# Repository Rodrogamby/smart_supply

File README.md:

# Dashboard

Dashboard for the project, built with HTML, CSS, JavaScript, Vite, and MQTT.js

The current prototype displays real sensor readings from an ESP32-S3 in the Channel 1 area

## Requirements

- Install [Node.js](https://nodejs.org/) with npm 
- An internet connection to reach the MQTT broker already running on Azure
- An ESP32 publishing measurements to see live readings

## Install and run

Open a terminal in the GUI folder containing `package.json`.

```sh
npm install
npm run dev
```

`npm install` installs the project's dependencies, including Vite and MQTT.js, and creates `node_modules`. 

Open the local URL printed by Vite. Keep the terminal running while using the dashboard. Press **Ctrl+C** to stop it; use `npm run dev` to start it again.

## Connect to MQTT

Enter these values in the dashboard and click **Connect**:

| Setting | Value |
| --- | --- |
| WebSocket URL | `wss://retotest.mexicocentral.cloudapp.azure.com:8084/mqtt` |
| Current test username | `reto` |
| Current test password | `reto` |
| Topic used by the JavaScript | `test2` |

These are temporary lol

The ESP32 sends MQTT over TLS on port **8883**. The browser uses MQTT over secure WebSockets on port **8084** to connect to the same broker.

## Measurement format

The ESP32 publishes JSON messages like this on `test2`:

```json
{
  "device": "device",
  "sensor": "sensor",
  "sample": 1,
  "adc_raw": 25798
}
```

## Project files

| File | Purpose |
| --- | --- |
| `index.html` | Dashboard structure |
| `src/style.css` | Styling and responsive layout |
| `src/main.js` | MQTT connection, message validation, and display updates |
| `package.json` | Dependencies and npm commands |
| `package-lock.json` | Locked dependency versions |

# Access the Virtual Machine

Use Tec Visitantes Network

```cmd
ssh -i "path of the  smart_supply\VM\vm1_key.pem file" azureuser@158.23.60.51
```

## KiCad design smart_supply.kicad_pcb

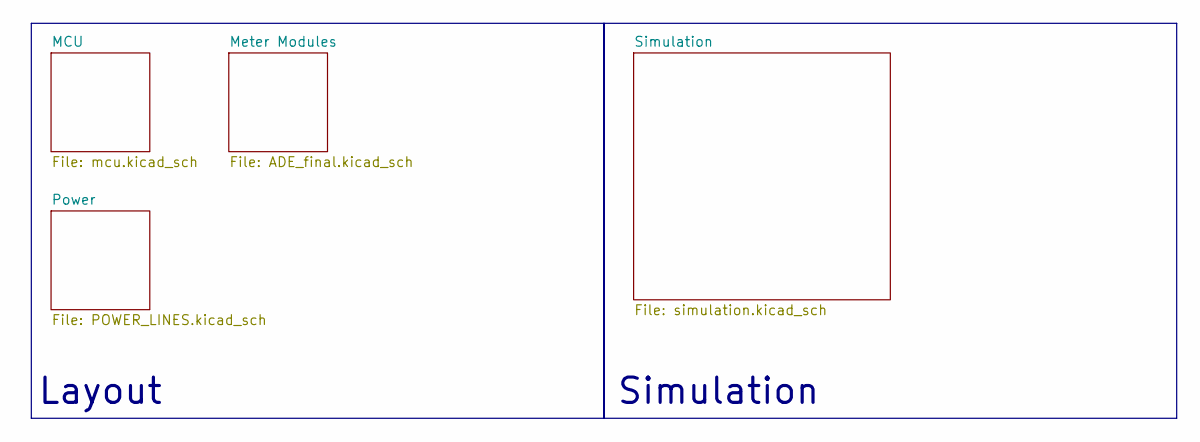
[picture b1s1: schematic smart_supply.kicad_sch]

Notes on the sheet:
Simulation
Layout

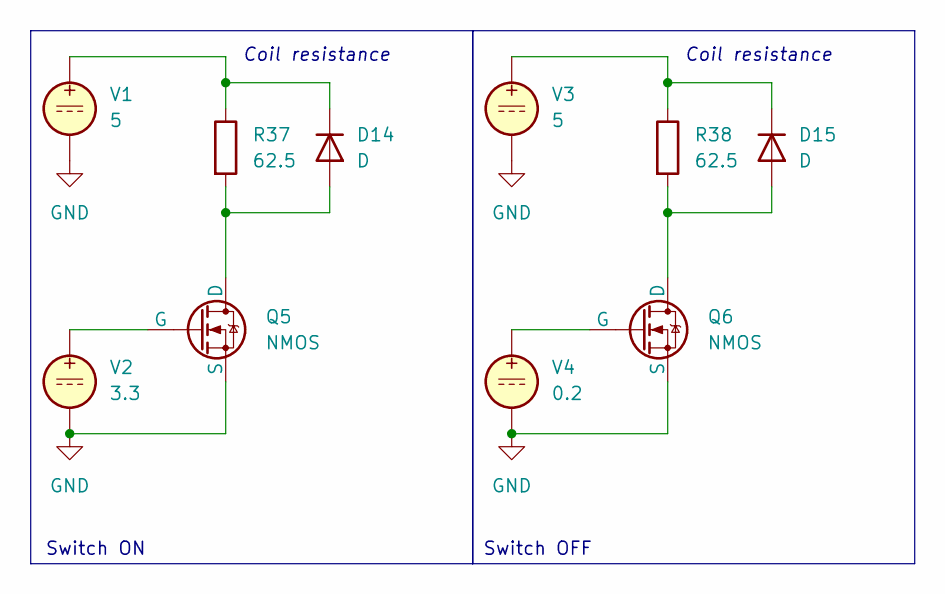
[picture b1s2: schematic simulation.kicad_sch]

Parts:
D14, D15: D
Q5, Q6: NMOS; Relay_SPST_Omron_G2RL-1A-E
R37, R38: 62.5
V1, V3: 5; TQFP-44_10x10mm_P0.8mm
V2: 3.3; TQFP-44_10x10mm_P0.8mm
V4: 0.2; TQFP-44_10x10mm_P0.8mm

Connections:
unnamed: D14.1 (K), R37.1, V1.1
unnamed: D14.2 (A), Q5.1 (D), R37.2
unnamed: D15.1 (K), R38.1, V3.1
unnamed: D15.2 (A), Q6.1 (D), R38.2
unnamed: Q5.2 (G), V2.1
unnamed: Q5.3 (S), Q6.3 (S), V1.2, V2.2, V3.2, V4.2
unnamed: Q6.2 (G), V4.1

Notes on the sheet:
Coil resistance
Switch OFF
Switch ON

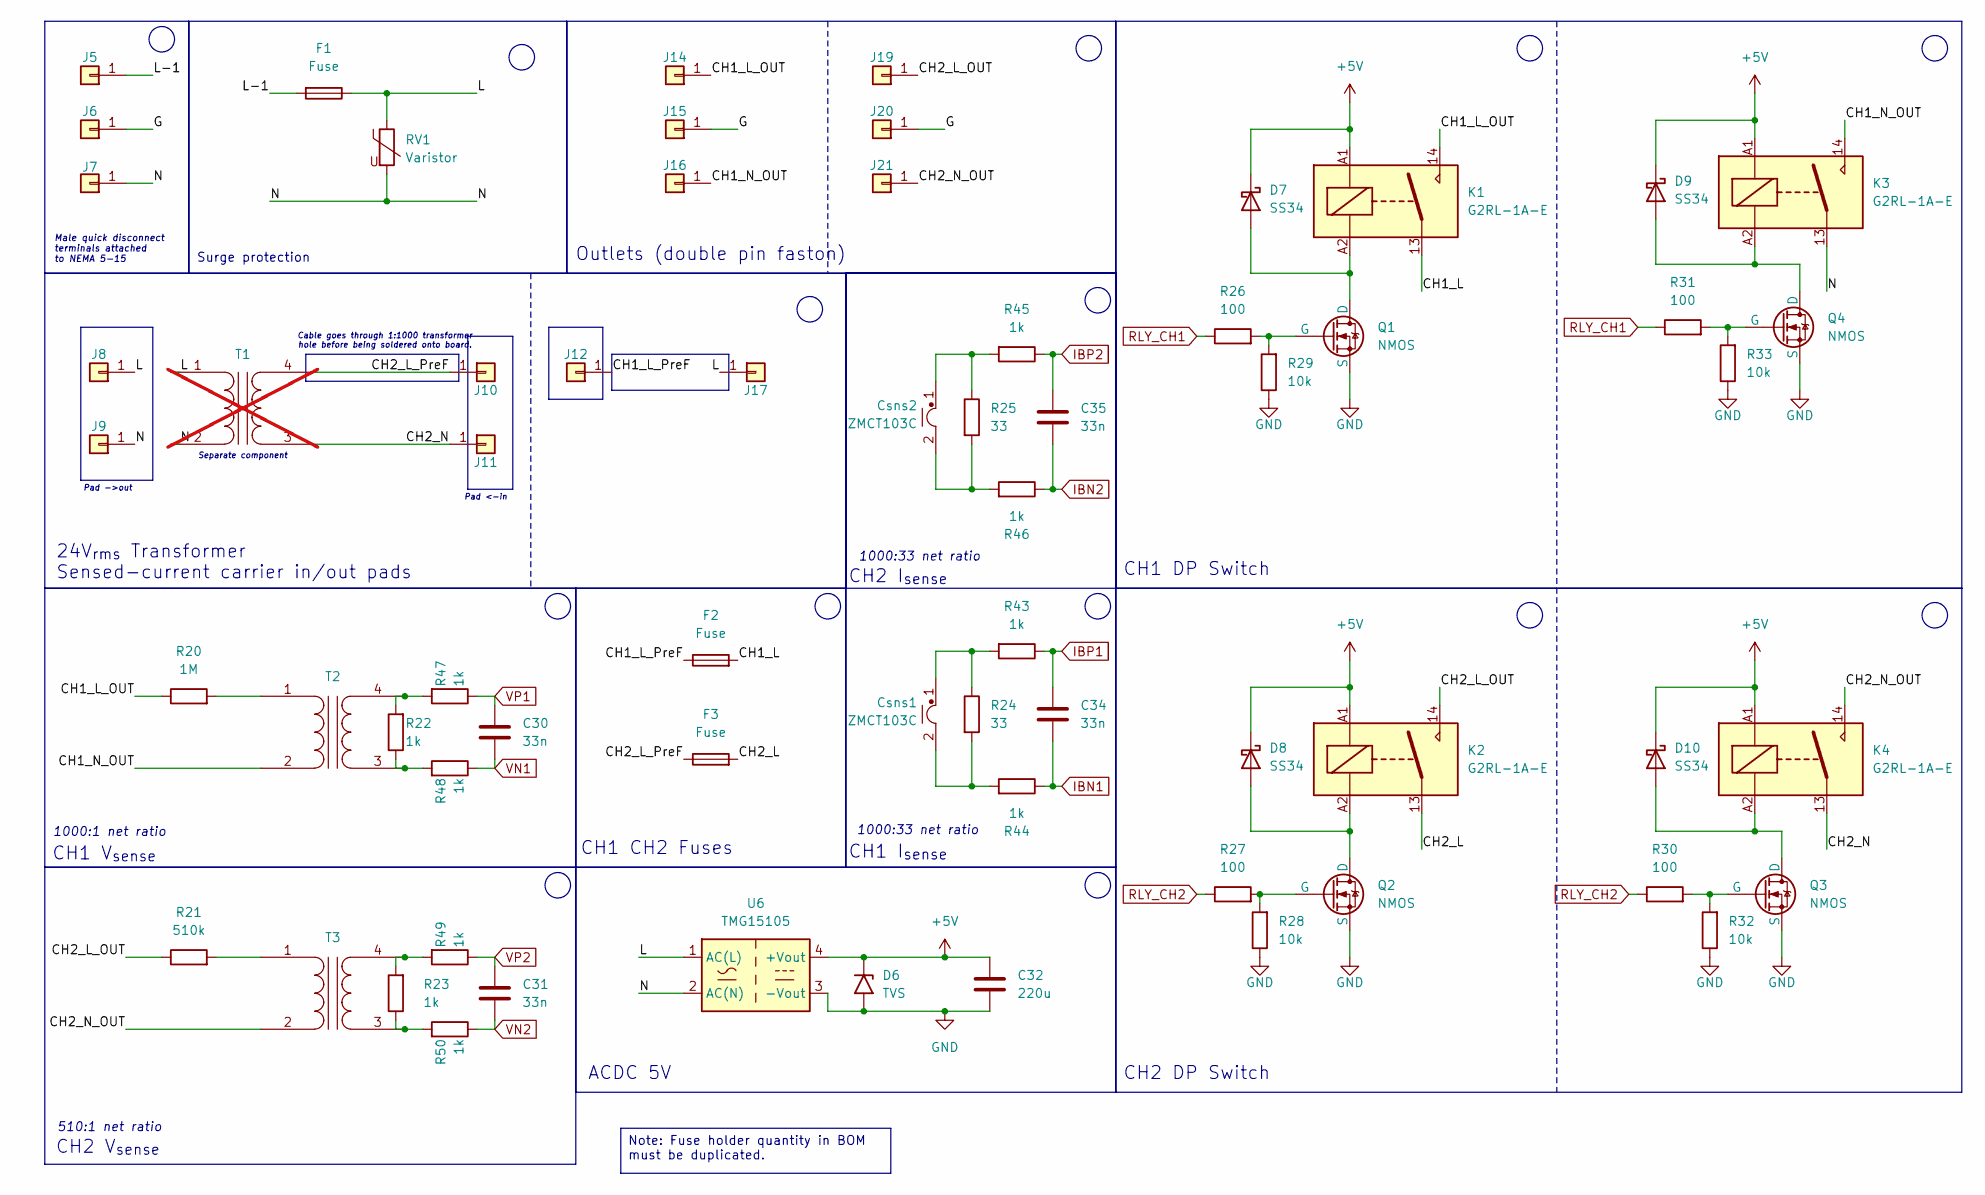
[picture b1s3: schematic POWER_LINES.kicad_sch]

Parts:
C30, C31, C34, C35: 33n; C_0402_1005Metric; MPN EMK105B7333KVHF; Mouser 963-EMK105B7333KVHF
C32: 220u; CP_Radial_D8.0mm_P3.50mm; MPN ESL227M035AG8AA; Mouser 80-ESL227M035AG8AA
Csns1, Csns2: ZMCT103C; Transformer_Zeming_ZMCT103C; MPN ZMCT103C
D6: TVS; D_SMF; MPN SMF5V0A-E3-08; Mouser 78-SMF5V0A-E3-08
D7, D8, D9, D10: SS34; D_SMA; MPN SS34; Mouser 512-SS34
F1, F2, F3: Fuse; Fuseholder_Littelfuse_100_series_5x20mm; MPN 01000020Z; Mouser 576-01000020Z
J5, J6, J7, J14, J15, J16, J19, J20, J21: Conn_01x01; 4901; MPN 4901; Mouser 534-4901
J8, J9, J10, J11, J12, J17: Conn_01x01; SolderWire-2sqmm_1x01_D2mm_OD3.9mm
K1, K2, K3, K4: G2RL-1A-E; Relay_SPST_Omron_G2RL-1A; MPN G2RL-1A-E DC5; Mouser 653-G2RL-1A-E-DC5
Q1, Q2, Q3, Q4: NMOS; SOT-23-3 (TO-236); MPN SI2302DDS-T1-GE3; Mouser 78-SI2302DDS-T1-GE3
R20: 1M; R_1206_3216Metric; MPN VT1206BRB071ML; Mouser 603-VT1206BRB071ML
R21: 510k; R_1206_3216Metric; MPN VT1206BRD07510KL; Mouser 603-VT1206BRD07510KL
R22, R23, R43, R44, R45, R46, R47, R48, R49, R50: 1k; R_0402_1005Metric; MPN RP0402BRD071KL; Mouser 603-RP0402BRD071KL
R24, R25: 33; R_0805_2012Metric; MPN ERA-6AHD330V; Mouser 667-ERA-6AHD330V
R26, R27, R30, R31: 100; R_0402_1005Metric; MPN CR0402JW-101GLF; Mouser 652-CR0402JW-101GLF
R28, R29, R32, R33: 10k; R_0402_1005Metric; MPN RC0402FR-7D10KL; Mouser 603-RC0402FR-7D10KL
RV1: Varistor; RV_Disc_D12mm_W3.9mm_P7.5mm; MPN B72210S0271K101; Mouser 871-B72210S271K101
T1: Transformer_1P_1S; not fitted
T2, T3: Transformer_1P_1S; Transformer_Zeming_ZMPT101K; MPN ZMPT101B
U6: TMG15105; Converter_ACDC_TRACO_TMG_151xx_THT; MPN TMG 15105; Mouser 495-TMG15105

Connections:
+5V: C32.1, D6.1 (A1), D7.1 (K), D8.1 (K), D9.1 (K), D10.1 (K), K1.A1, K2.A1, K3.A1, K4.A1, U6.4 (+Vout); also elsewhere on the board
/Power/CH1_L: F2.2, K1.13
/Power/CH1_L_OUT: J14.1 (Pin_1_1), K1.14, R20.1
/Power/CH1_L_PreF: F2.1, J12.1 (Pin_1_1)
/Power/CH1_N_OUT: J16.1 (Pin_1_1), K3.14, T2.2 (AB)
/Power/CH2_L: F3.2, K2.13
/Power/CH2_L_OUT: J19.1 (Pin_1_1), K2.14, R21.1
/Power/CH2_L_PreF: F3.1, J10.1 (Pin_1_1), T1.4 (SB)
/Power/CH2_N: J11.1 (Pin_1_1), K4.13, T1.3 (SA)
/Power/CH2_N_OUT: J21.1 (Pin_1_1), K4.14, T3.2 (AB)
/Power/G: J6.1 (Pin_1_1), J15.1 (Pin_1_1), J20.1 (Pin_1_1)
/Power/L: F1.1, J8.1 (Pin_1_1), J17.1 (Pin_1_1), RV1.1, T1.1 (AA), U6.1 (AC(L))
/Power/L-1: F1.2, J5.1 (Pin_1_1)
/Power/N: J7.1 (Pin_1_1), J9.1 (Pin_1_1), K3.13, RV1.2, T1.2 (AB), U6.2 (AC(N))
GND: C32.2, D6.2 (A2), Q1.3 (S), Q2.3 (S), Q3.3 (S), Q4.3 (S), R28.1, R29.1, R32.1, R33.1, U6.3 (-Vout); also elsewhere on the board
IBN1: C34.2, R44.1; also elsewhere on the board
IBN2: C35.2, R46.1; also elsewhere on the board
IBP1: C34.1, R43.1; also elsewhere on the board
IBP2: C35.1, R45.1; also elsewhere on the board
unnamed: Csns1.1, R24.1, R43.2
unnamed: Csns1.2, R24.2, R44.2
unnamed: Csns2.1, R25.1, R45.2
unnamed: Csns2.2, R25.2, R46.2
unnamed: D7.2 (A), K1.A2, Q1.1 (D)
unnamed: D8.2 (A), K2.A2, Q2.1 (D)
unnamed: D9.2 (A), K3.A2, Q4.1 (D)
unnamed: D10.2 (A), K4.A2, Q3.1 (D)
unnamed: Q1.2 (G), R26.2, R29.2
unnamed: Q2.2 (G), R27.2, R28.2
unnamed: Q3.2 (G), R30.2, R32.2
unnamed: Q4.2 (G), R31.2, R33.2
unnamed: R20.2, T2.1 (AA)
unnamed: R22.1, R48.2, T2.3 (SA)
unnamed: R22.2, R47.2, T2.4 (SB)
unnamed: R21.2, T3.1 (AA)
unnamed: R23.1, R50.2, T3.3 (SA)
unnamed: R23.2, R49.2, T3.4 (SB)
RLY_CH1: R26.1, R31.1; also elsewhere on the board
RLY_CH2: R27.1, R30.1; also elsewhere on the board
VN1: C30.2, R48.1; also elsewhere on the board
VN2: C31.2, R50.1; also elsewhere on the board
VP1: C30.1, R47.1; also elsewhere on the board
VP2: C31.1, R49.1; also elsewhere on the board

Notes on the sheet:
Pad ->out
Cable goes through 1:1000 transformer hole before being soldered onto board.
24V_{rms} Transformer Sensed-current carrier in/out pads
CH2 V_{sense}
CH1 CH2 Fuses
Separate component
Surge protection
1000:1 net ratio
1000:33 net ratio
ACDC 5V
Male quick disconnect terminals attached to NEMA 5-15
Pad <-in
CH1 V_{sense}
CH1 DP Switch
CH1 I_{sense}
CH2 I_{sense}
CH2 DP Switch
510:1 net ratio
Outlets (double pin faston)
Note: Fuse holder quantity in BOM must be duplicated.

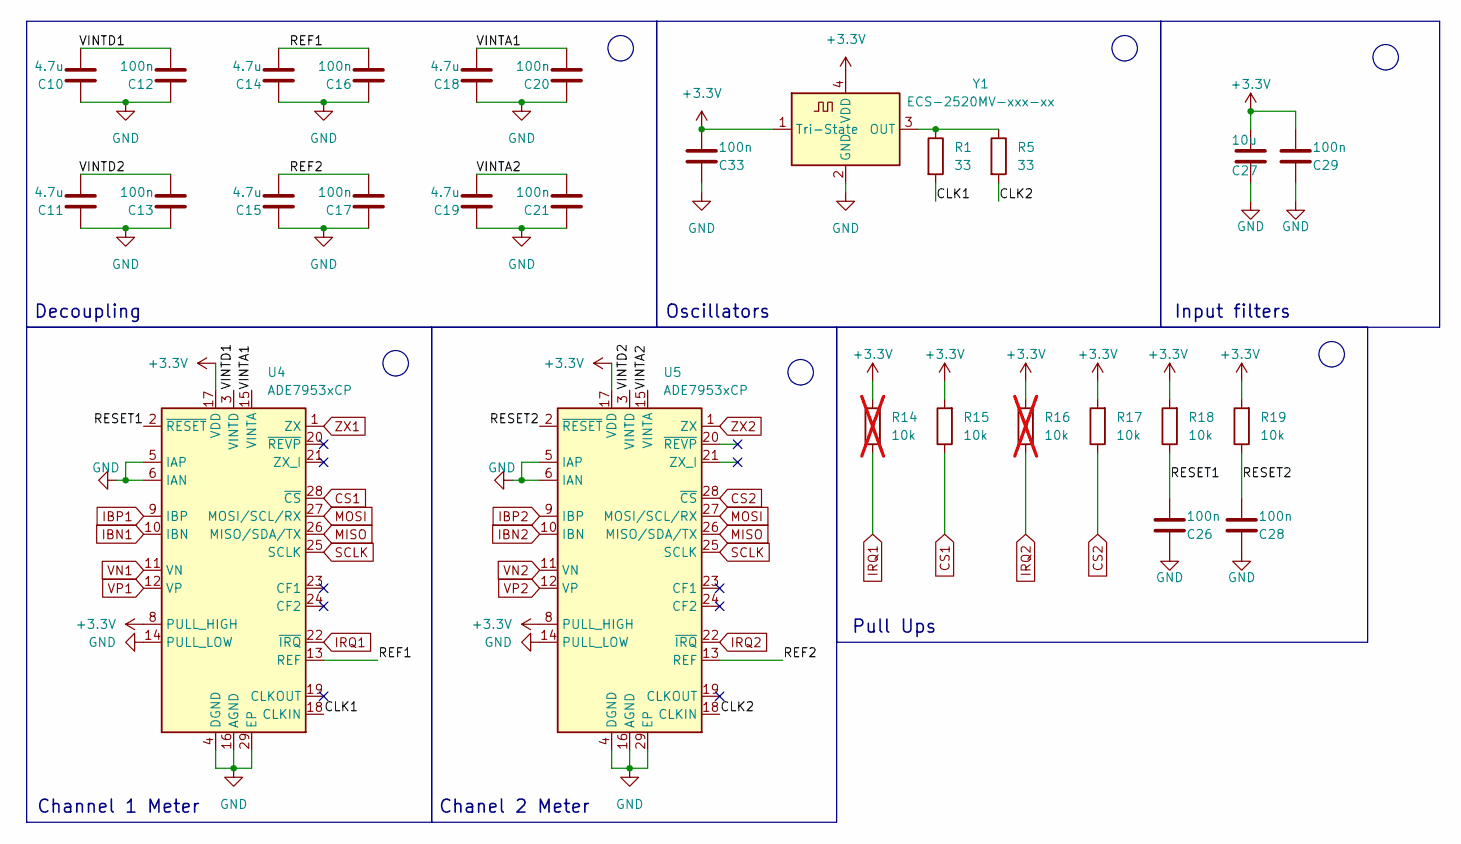
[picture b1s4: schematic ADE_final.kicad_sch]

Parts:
C10: 4.7u; C_0402_1005Metric; MPN CL05A475MO5LUNC
C11, C14, C15, C18, C19: 4.7u; C_0402_1005Metric; MPN CL05A475MO5LUNC; Mouser 187-CL05A475MO5LUNC
C12, C13, C16, C17, C20, C21, C26, C28, C29, C33: 100n; C_0402_1005Metric; MPN CC0402KRX7R7BB104; Mouser 603-CC402KRX7R7BB104
C27: 10u; C_0603_1608Metric; MPN C0603C106J3RACTU; Mouser 80-C0603C106J3RACTU
R1, R5: 33; R_0402_1005Metric; MPN AR0402JR-0733RL; Mouser 603-AR0402JR-0733RL
R14, R16: 10k; R_0402_1005Metric; MPN ESR01MZPF1002; not fitted
R15, R17, R18, R19: 10k; R_0402_1005Metric; MPN RC0402FR-7D10KL; Mouser 603-RC0402FR-7D10KL
U4, U5: ADE7953xCP; LFCSP-28-1EP_5x5mm_P0.5mm_EP3.14x3.14mm; MPN ADE7953ACPZ; Mouser 584-ADE7953ACPZ-R
Y1: ECS-2520MV-xxx-xx; Oscillator_SMD_ECS_2520MV-xxx-xx-4Pin_2.5x2.0mm; MPN ECS-2033-035-AU; Mouser 520-2033-035-AU

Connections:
+3.3V: C27.1, C29.2, C33.2, R14.2, R15.2, R16.2, R17.2, R18.2, R19.2, U4.7 (PULL_HIGH), U4.8 (PULL_HIGH), U4.17 (VDD), U5.7 (PULL_HIGH), U5.8 (PULL_HIGH), U5.17 (VDD), Y1.1 (Tri-State), Y1.4 (VDD); also elsewhere on the board
/Meter Modules/CLK1: R1.2, U4.18 (CLKIN)
/Meter Modules/CLK2: R5.2, U5.18 (CLKIN)
/Meter Modules/REF1: C14.2, C16.2, U4.13 (REF)
/Meter Modules/REF2: C15.2, C17.2, U5.13 (REF)
/Meter Modules/RESET1: C26.2, R18.1, U4.2 (~RESET)
/Meter Modules/RESET2: C28.2, R19.1, U5.2 (~RESET)
/Meter Modules/VINTA1: C18.2, C20.2, U4.15 (VINTA)
/Meter Modules/VINTA2: C19.2, C21.2, U5.15 (VINTA)
/Meter Modules/VINTD1: C10.2, C12.2, U4.3 (VINTD)
/Meter Modules/VINTD2: C11.2, C13.2, U5.3 (VINTD)
CS1: R15.1, U4.28 (~CS); also elsewhere on the board
CS2: R17.1, U5.28 (~CS); also elsewhere on the board
GND: C10.1, C11.1, C12.1, C13.1, C14.1, C15.1, C16.1, C17.1, C18.1, C19.1, C20.1, C21.1, C26.1, C27.2, C28.1, C29.1, C33.1, U4.4 (DGND), U4.5 (IAP), U4.6 (IAN), U4.14 (PULL_LOW), U4.16 (AGND), U4.29 (EP), U5.4 (DGND), U5.5 (IAP), U5.6 (IAN), U5.14 (PULL_LOW), U5.16 (AGND), U5.29 (EP), Y1.2 (GND); also elsewhere on the board
IBN1: U4.10 (IBN); also elsewhere on the board
IBN2: U5.10 (IBN); also elsewhere on the board
IBP1: U4.9 (IBP); also elsewhere on the board
IBP2: U5.9 (IBP); also elsewhere on the board
IRQ1: R14.1, U4.22 (~IRQ); also elsewhere on the board
IRQ2: R16.1, U5.22 (~IRQ); also elsewhere on the board
MISO: U4.26 (MISO/SDA/TX), U5.26 (MISO/SDA/TX); also elsewhere on the board
MOSI: U4.27 (MOSI/SCL/RX), U5.27 (MOSI/SCL/RX); also elsewhere on the board
unnamed: R1.1, R5.1, Y1.3 (OUT)
SCLK: U4.25 (SCLK), U5.25 (SCLK); also elsewhere on the board
VN1: U4.11 (VN); also elsewhere on the board
VN2: U5.11 (VN); also elsewhere on the board
VP1: U4.12 (VP); also elsewhere on the board
VP2: U5.12 (VP); also elsewhere on the board
ZX1: U4.1 (ZX); also elsewhere on the board
ZX2: U5.1 (ZX); also elsewhere on the board

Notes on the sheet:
Decoupling
Pull Ups
Input filters
Channel 1 Meter
Chanel 2 Meter
Oscillators

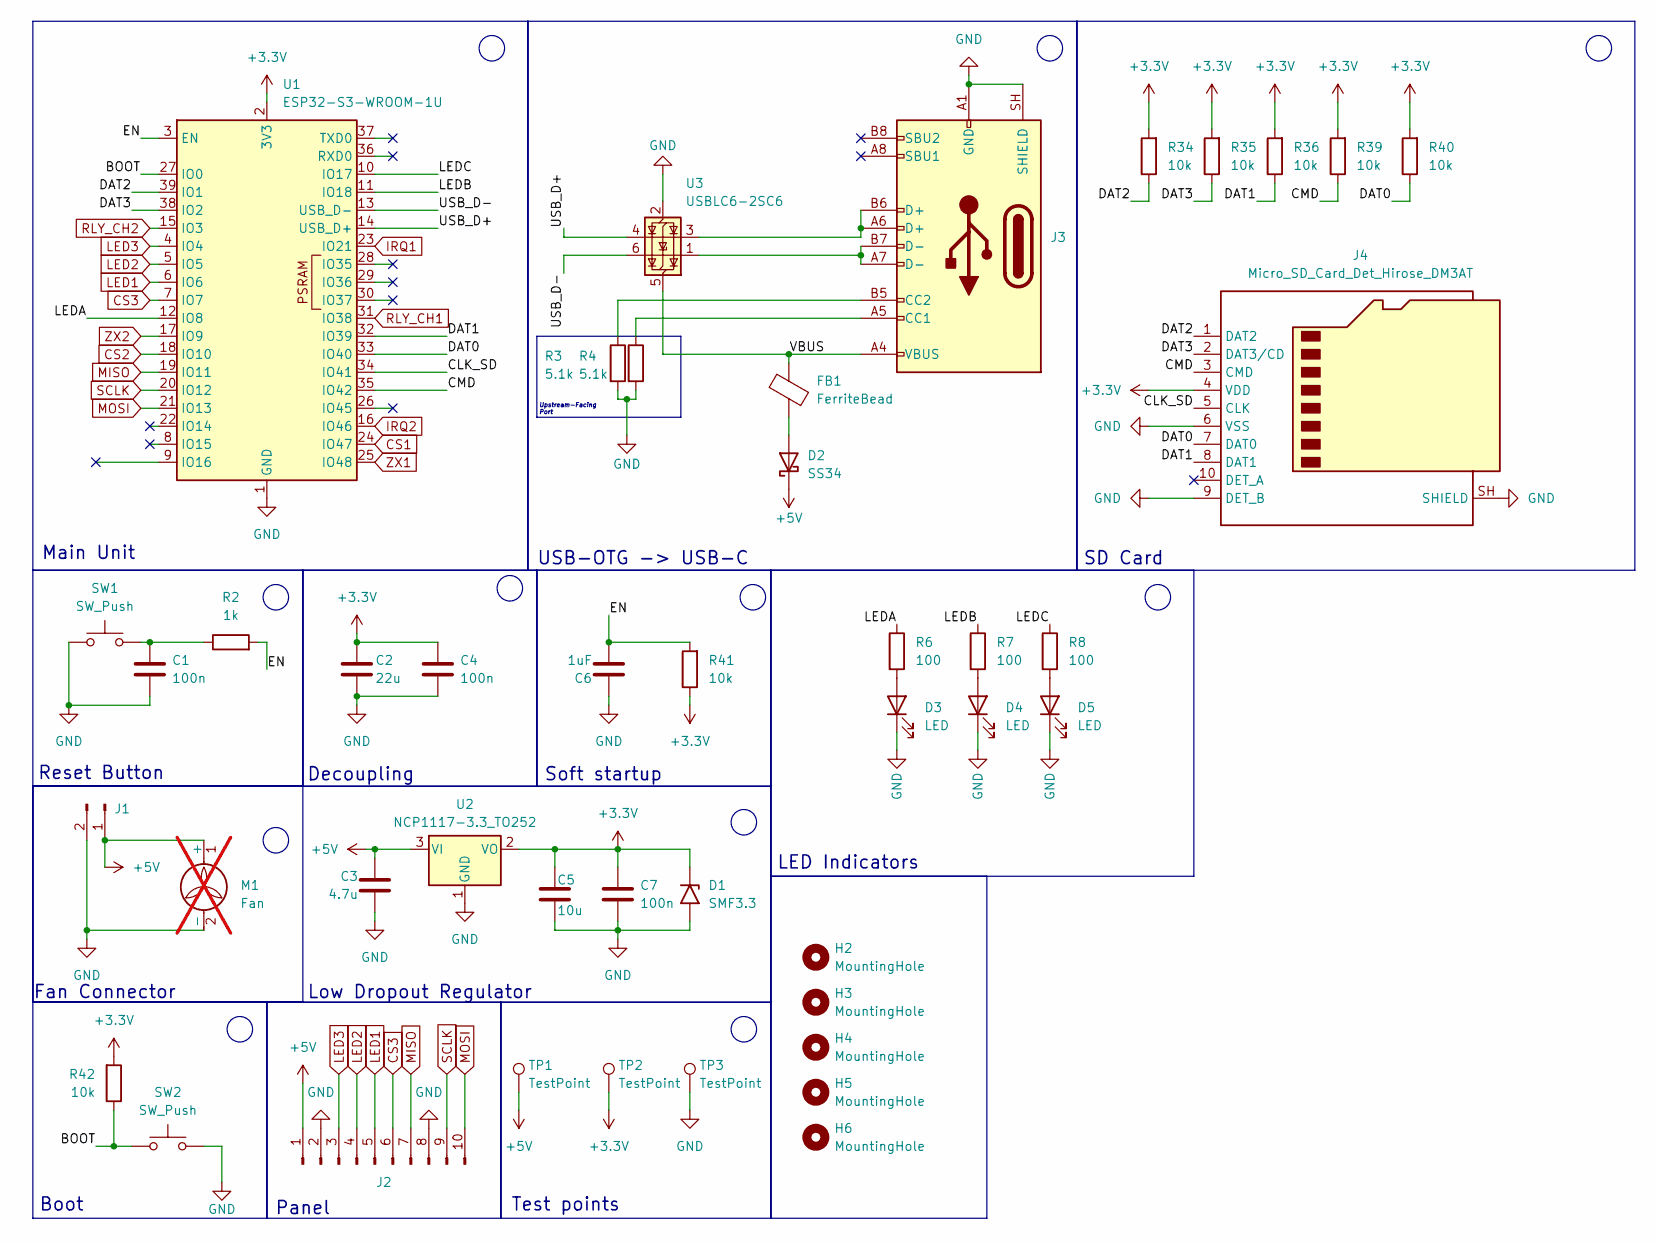
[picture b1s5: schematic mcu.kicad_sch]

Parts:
C1, C4, C7: 100n; C_0402_1005Metric; MPN CC0402KRX7R7BB104; Mouser 603-CC402KRX7R7BB104
C2: 22u; C_1206_3216Metric; MPN CL31A226KAHNNNE; Mouser 187-CL31A226KAHNNNE
C3: 4.7u; C_0805_2012Metric; MPN CL21A475KAQNNNE; Mouser 187-CL21A475KAQNNNE
C5: 10u; C_1206_3216Metric; MPN C1206C106J3RACTU; Mouser 80-C1206C106J3RACTU
C6: 1uF; C_0805_2012Metric; MPN CL21B105KAFNFNE; Mouser 187-CL21B105KAFNFNE
D1: SMF3.3; D_SMF; MPN SMF3.3; Mouser 576-SMF3.3
D2: SS34; D_SMA; MPN SS34; Mouser 512-SS34
D3, D4, D5: LED; LED_0805_2012Metric; MPN LTST-C170KRKT; Mouser 859-LTST-C170KRKT
FB1: FerriteBead; C_0805_2012Metric; MPN BLM21PG221SN1D; Mouser 81-BLM21P221SG
H2, H3, H4, H5, H6: MountingHole; MountingHole_3.2mm_M3
J1: Conn_01x02_Pin; JST_XH_B2B-XH-A_1x02_P2.50mm_Vertical; MPN B2B-XH-A(LF)(SN); Mouser 306-B2BXHALFSNP
J2: Conn_01x10_Pin; B10B-XH-A(LF)(SN); MPN B10B-XH-A(LF)(SN); Mouser 306-B10BXHALFSNP
J3: USB_C_Receptacle_USB2.0_16P; USB_C_Receptacle_GCT_USB4105-xx-A_16P_TopMnt_Horizontal; MPN USB4105-GF-A; Mouser 640-USB4105-GF-A
J4: Micro_SD_Card_Det_Hirose_DM3AT; microSD_HC_Hirose_DM3AT-SF-PEJM5; MPN DM3AT-SF-PEJM5; Mouser 798-DM3AT-SF-PEJM5
M1: Fan; not fitted
R2: 1k; R_0402_1005Metric; MPN RP0402BRD071KL; Mouser 603-RP0402BRD071KL
R3, R4: 5.1k; R_0402_1005Metric; MPN RMC10K512FTH; Mouser 791-RMC10K512FTH
R6, R7, R8: 100; R_0805_2012Metric; MPN CR0805-JW-101ELF; Mouser 652-CR0805JW-101ELF
R34, R35, R36, R39, R40, R41, R42: 10k; R_0402_1005Metric; MPN RC0402FR-7D10KL; Mouser 603-RC0402FR-7D10KL
SW1, SW2: SW_Push; SW_SPST_Omron_B3FS-101xP; MPN B3FS-1010P; Mouser 653-B3FS-1010P
TP1, TP2, TP3: TestPoint; TestPoint_Loop_D2.50mm_Drill1.0mm; MPN 5002; Mouser 534-5002
U1: ESP32-S3-WROOM-1U; MPN ESP32-S3-WROOM-1U-N8R8; Mouser 356-ESP32S3WRM1UN8R8
U2: NCP1117-3.3_TO252; TO-252-2; MPN NCP1117DT33T5G; Mouser 863-NCP1117DT33T5G
U3: USBLC6-2SC6; SOT-23-6; MPN USBLC6-2SC6; Mouser 511-USBLC6-2SC6

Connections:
+3.3V: C2.1, C4.1, C5.1, C7.1, D1.1 (A1), J4.4 (VDD), R34.2, R35.2, R36.2, R39.2, R40.2, R41.1, R42.2, TP2.1 (1_1), U1.2 (3V3), U2.2 (VO); also elsewhere on the board
+5V: C3.1, D2.1 (K), J1.1, J2.1, M1.1 (+), TP1.1 (1_1), U2.3 (VI); also elsewhere on the board
/MCU/BOOT: R42.1, SW2.1, U1.27 (IO0)
/MCU/CLK_SD: J4.5 (CLK), U1.34 (IO41)
/MCU/CMD: J4.3 (CMD), R39.1, U1.35 (IO42)
/MCU/DAT0: J4.7 (DAT0), R40.1, U1.33 (IO40)
/MCU/DAT1: J4.8 (DAT1), R36.1, U1.32 (IO39)
/MCU/DAT2: J4.1 (DAT2), R34.1, U1.39 (IO1)
/MCU/DAT3: J4.2 (DAT3/CD), R35.1, U1.38 (IO2)
/MCU/EN: C6.2, R2.2, R41.2, U1.3 (EN)
/MCU/LEDA: R6.1, U1.12 (IO8)
/MCU/LEDB: R7.1, U1.11 (IO18)
/MCU/LEDC: R8.1, U1.10 (IO17)
/MCU/USB_D+: U1.14 (USB_D+), U3.4 (I/O2)
/MCU/USB_D-: U1.13 (USB_D-), U3.6 (I/O1)
/MCU/VBUS: FB1.1, J3.A4 (VBUS), J3.A9 (VBUS), J3.B4 (VBUS), J3.B9 (VBUS), U3.5 (VBUS)
CS1: U1.24 (IO47); also elsewhere on the board
CS2: U1.18 (IO10); also elsewhere on the board
CS3: J2.6, U1.7 (IO7)
GND: C1.2, C2.2, C3.2, C4.2, C5.2, C6.1, C7.2, D1.2 (A2), D3.1 (K), D4.1 (K), D5.1 (K), J1.2, J2.2, J2.8, J3.A1 (GND), J3.A12 (GND), J3.B1 (GND), J3.B12 (GND), J3.SH (SHIELD), J4.6 (VSS), J4.9 (DET_B), J4.SH (SHIELD), M1.2 (-), R3.2, R4.2, SW1.1, SW2.2, TP3.1 (1_1), U1.1 (GND), U1.40 (GND), U1.41 (GND), U2.1 (GND), U3.2 (GND); also elsewhere on the board
IRQ1: U1.23 (IO21); also elsewhere on the board
IRQ2: U1.16 (IO46); also elsewhere on the board
LED1: J2.5, U1.6 (IO6)
LED2: J2.4, U1.5 (IO5)
LED3: J2.3, U1.4 (IO4)
MISO: J2.7, U1.19 (IO11); also elsewhere on the board
MOSI: J2.10, U1.21 (IO13); also elsewhere on the board
unnamed: C1.1, R2.1, SW1.2
unnamed: D2.2 (A), FB1.2
unnamed: D3.2 (A), R6.2
unnamed: D4.2 (A), R7.2
unnamed: D5.2 (A), R8.2
unnamed: J3.A5 (CC1), R4.1
unnamed: J3.B5 (CC2), R3.1
unnamed: J3.A6 (D+), J3.B6 (D+), U3.3 (I/O2)
unnamed: J3.A7 (D-), J3.B7 (D-), U3.1 (I/O1)
RLY_CH1: U1.31 (IO38); also elsewhere on the board
RLY_CH2: U1.15 (IO3); also elsewhere on the board
SCLK: J2.9, U1.20 (IO12); also elsewhere on the board
ZX1: U1.25 (IO48); also elsewhere on the board
ZX2: U1.17 (IO9); also elsewhere on the board

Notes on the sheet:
Panel
Fan Connector
Low Dropout Regulator
Boot
Upstream-Facing Port
USB-OTG -> USB-C
LED Indicators
Test points
SD Card
Reset Button
Decoupling
Main Unit
Soft startup

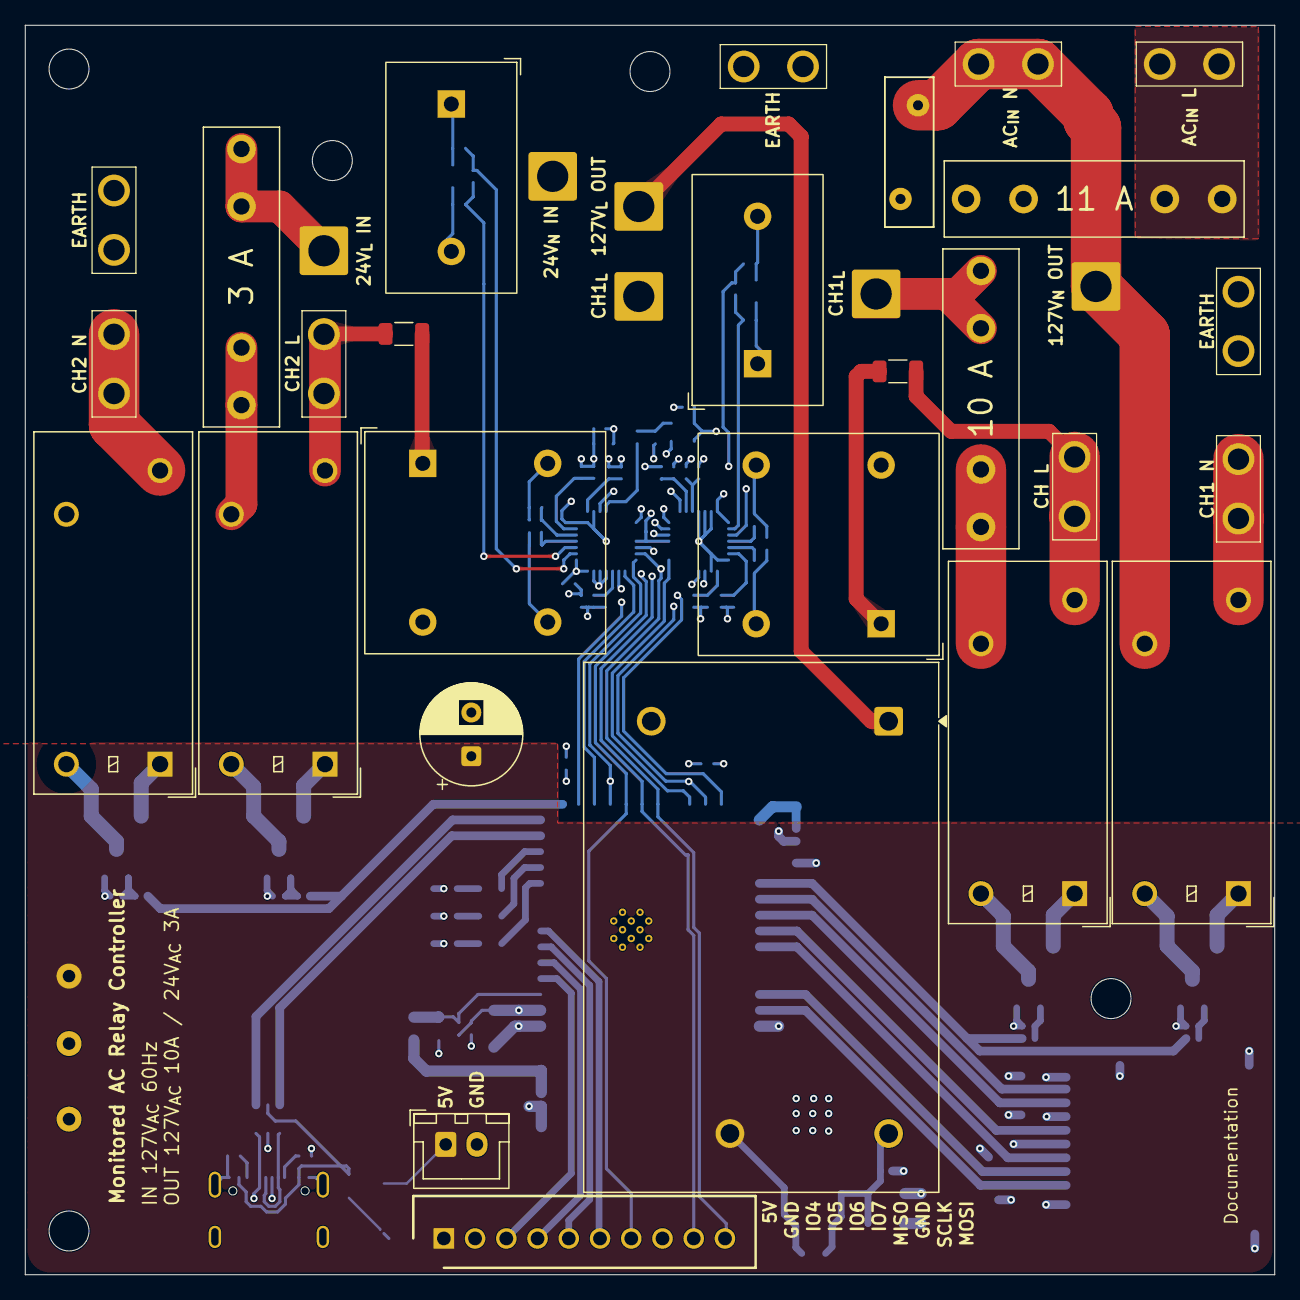
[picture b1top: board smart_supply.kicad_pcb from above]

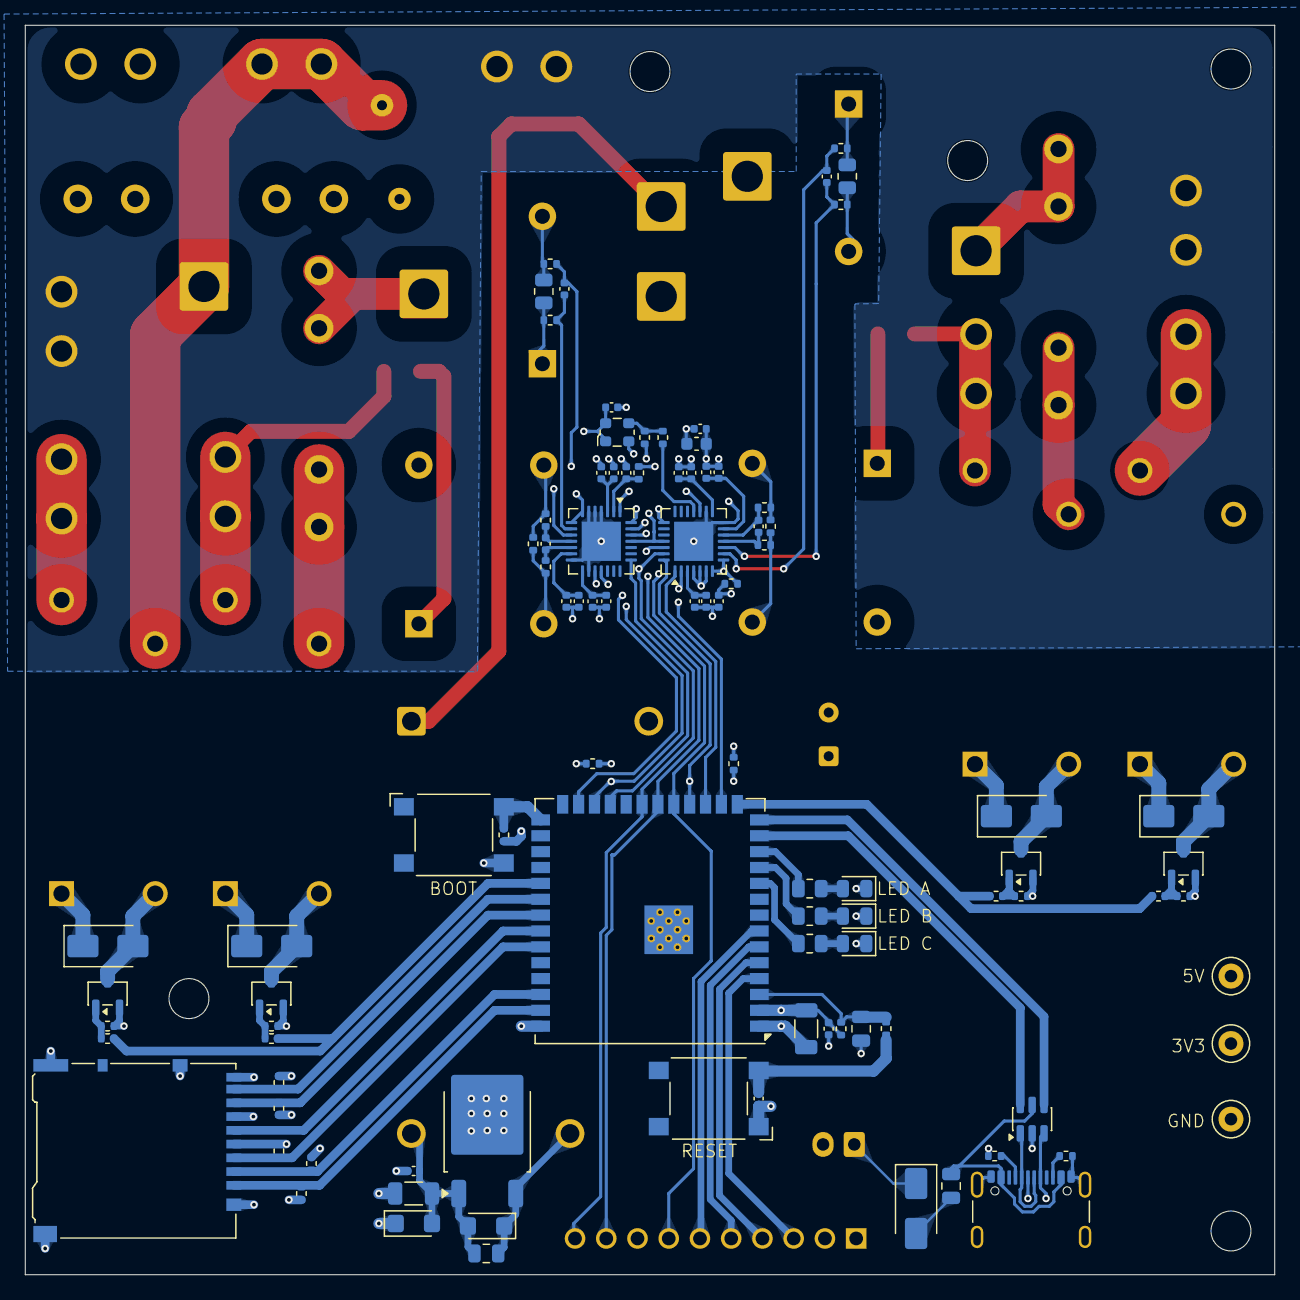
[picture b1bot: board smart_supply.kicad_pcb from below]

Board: 4 copper layers, 100.0 x 100.0 mm, 133 parts (95 on the bottom side), 91 nets.

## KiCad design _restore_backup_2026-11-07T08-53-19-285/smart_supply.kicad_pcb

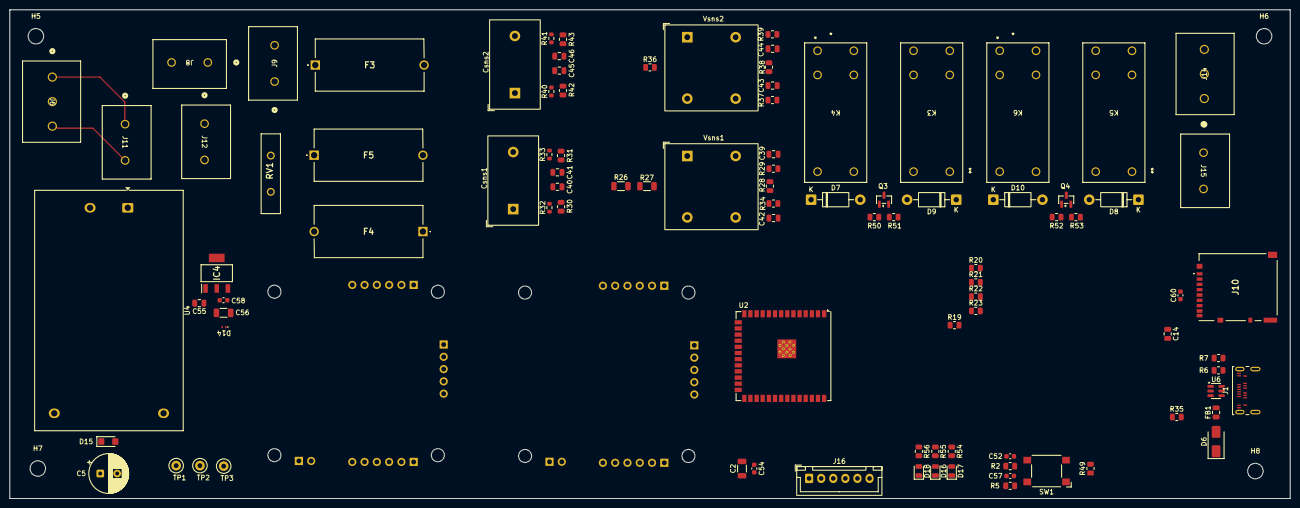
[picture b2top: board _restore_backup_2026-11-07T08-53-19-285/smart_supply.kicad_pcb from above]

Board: 4 copper layers, 264.8 x 101.1 mm, 103 parts (1 on the bottom side), 74 nets.

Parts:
C2: 22u; C_1206_3216Metric
C5: 220u; CP_Radial_D8.0mm_P3.50mm
C14: 10u; C_0805_2012Metric
C39, C40, C41, C42, C43, C44, C45, C46: 33n; C_0805_2012Metric
C52, C54, C57, C58, C60: 100n; C_0603_1608Metric
C55: 4.7u; C_0805_2012Metric
C56: 10u; C_1206_3216Metric
Csns1, Csns2: ZMCT103C; Transformer_Zeming_ZMCT103C
D6: SS34; D_SMA
D7, D8, D9, D10: 1N4007; D_DO-41_SOD81_P10.16mm_Horizontal
D14: TPD1E10B06DPYR; Texas_DPY0002A_0.6x1mm_P0.65mm
D15: SMF5V0A; D_SMF
D16, D17, D18: LED; LED_0805_2012Metric
F3, F4, F5: Fuse; fuse holder
FB1: FerriteBead; C_0805_2012Metric
H5, H6, H7, H8: MountingHole; MountingHole_3.2mm_M3
IC4: MIC39100-3.3WS; SOT230P700X180-4N
J1: USB_C_Receptacle_USB2.0_16P; USB_C_Receptacle_Amphenol_124019772112A
J6, J14: 1730405; CONN_1730405_PXC
J8, J9, J11, J12, J15: 1717020; CONN_1717020_PXC
J10: DM3AT-SF-PEJM5; DM3ATSFPEJM5
J16: Conn_01x06_Pin; JST_XH_B6B-XH-A_1x06_P2.50mm_Vertical
J17, J18: Conn_01x19_Pin; breakoutHOLES
K3, K4, K5, K6: G2R-1A-E DC5; RELAY_G2R-1A-E AC12_OMR
Q3, Q4: AO3400A; SOT-23
R2: 0; R_0805_2012Metric
R5, R19, R20, R21, R22, R23, R49: 10k; R_0805_2012Metric
R6, R7: 5.1k; R_0805_2012Metric
R26, R27: 47k; R_1206_3216Metric
R28, R38, R50, R52: 100; R_0805_2012Metric
R29, R30, R31, R34, R37, R39, R42, R43: 1k; R_0805_2012Metric
R32, R33: 10; R_0603_1608Metric
R35: 1.5k; R_0805_2012Metric
R36: 20k; R_0805_2012Metric
R40, R41: 33; R_0603_1608Metric
R51, R53: 100k; R_0805_2012Metric
R54, R55, R56: 470; R_0805_2012Metric
RV1: MOV-14D241K; MOV14D241K
SW1, SW2: SW_Push; SW_SPST_Omron_B3FS-100xP
TP1, TP2, TP3: TestPoint; TestPoint_Loop_D2.50mm_Drill1.0mm
U2: ESP32-S3-WROOM-1U
U4: HLK-10M05; Converter_ACDC_Hi-Link_HLK-10Mxx
U6: USBLC6-2SC6; SOT-23-6
Vsns1, Vsns2: ZMPT101K; Transformer_Zeming_ZMPT101K

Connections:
+3.3V: C2.1, C14.1, C54.1, C56.1, C58.2, C60.2, D14.1, IC4.3 (OUT), J10.4 (VDD), R5.2, R19.1, R20.1, R21.1, R22.1, R23.1, R35.1, R49.1, TP2.1 (1_1), U2.2 (3V3)
+5V: C5.1, C55.1, D6.1 (K), D7.1 (K), D8.1 (K), D9.1 (K), D10.1 (K), D15.1 (A1), IC4.1 (IN), J17.19, J18.19, K3.8, K4.8, K5.8, K6.8, TP1.1 (1_1), U4.4 (+Vout)
/MCU/BOOT: R49.2, SW2.1, U2.27 (IO0)
/MCU/CMD: J10.3 (CMD), R22.2
/MCU/D0_SD: J10.7 (DAT0), R23.2
/MCU/DAT1: J10.8 (DAT1), R21.2
/MCU/DAT2: J10.1 (DAT2), R19.2
/MCU/DAT3: J10.2 (CD/DAT3), R20.2
/MCU/EN: C57.2, R2.2, R5.1, U2.3 (EN)
/MCU/LEDF: R55.1, U2.5 (IO5)
/MCU/LEDSD: R56.1, U2.6 (IO6)
/MCU/LEDW: R54.1, U2.4 (IO4)
/MCU/USB_D+: U2.14 (USB_D+), U6.4 (I/O2)
/MCU/USB_D-: U2.13 (USB_D-), U6.6 (I/O1)
/POWER LINES/CH1_L_OUT: J14.1, K4.4, K4.5
/POWER LINES/CH1_N_OUT: J14.3, K3.4, K3.5
/POWER LINES/CH2_L: F3.2, K5.3, K5.6, R36.1
/POWER LINES/CH2_L_OUT: J15.1, K5.4, K5.5
/POWER LINES/CH2_N: J9.1, K6.3, K6.6, Vsns2.2
/POWER LINES/CH2_N_OUT: J15.2, K6.4, K6.5
/POWER LINES/L: J6.1, J11.1
/POWER LINES/N: J6.3, J11.2
CH1_L: F4.1, F5.2, K4.3, K4.6, R26.1
CH1_N: J8.1, J12.2, K3.3, K3.6, RV1.1, U4.2 (AC/N), Vsns1.2
CS1: J17.7, U2.18 (IO10)
CS2: J18.7, U2.10 (IO17)
GND: C2.2, C5.2, C14.2, C39.2, C40.2, C41.2, C42.2, C43.2, C44.2, C45.2, C46.2, C52.2, C54.2, C55.2, C56.2, C57.1, C58.1, C60.1, D14.2, D15.2 (A2), D16.1 (K), D17.1 (K), D18.1 (K), IC4.2 (GND_1), IC4.4 (GND_2), J1.A1 (GND), J1.A12 (GND), J1.B1 (GND), J1.B12 (GND), J1.SH (SHIELD), J10.6 (VSS), J10.MP1, J10.MP2, J10.MP3, J10.MP4, J10.MP5, J10.MP6, J16.6, J17.3, J17.4, J17.18, J18.3, J18.4, J18.18, Q3.2 (S), Q4.2 (S), R6.2, R7.2, R28.1, R32.2, R33.1, R34.2, R37.2, R38.2, R40.2, R41.1, R51.2, R53.2, SW1.1, SW2.2, TP3.1 (1_1), U2.1 (GND), U2.40 (GND), U2.41 (GND), U4.3 (-Vout), U6.2 (GND), Vsns1.3, Vsns2.3
IAN1: C41.1, J17.2, R31.1
IAN2: C46.1, J18.2, R43.1
IAP1: C40.1, J17.1, R30.1
IAP2: C45.1, J18.1, R42.1
IRQ1: J17.15, U2.22 (IO14)
IRQ2: J18.15, U2.11 (IO18)
LED1: J16.3, U2.7 (IO7)
LED2: J16.2, U2.12 (IO8)
LED3: J16.1, U2.17 (IO9)
MISO: J17.9, J18.9, U2.21 (IO13)
MOSI: J17.8, J18.8, U2.19 (IO11)
unnamed: C52.1, R2.1, SW1.2
unnamed: Csns1.1, R30.2, R32.1
unnamed: Csns1.2, R31.2, R33.2
unnamed: Csns2.1, R40.1, R42.2
unnamed: Csns2.2, R41.2, R43.2
unnamed: D6.2 (A), FB1.2
unnamed: D7.2 (A), D9.2 (A), K3.1, K4.1, Q3.3 (D)
unnamed: D8.2 (A), D10.2 (A), K5.1, K6.1, Q4.3 (D)
unnamed: D16.2 (A), R54.2
unnamed: D17.2 (A), R55.2
unnamed: D18.2 (A), R56.2
unnamed: F3.1, J9.2
unnamed: F5.1, J8.2, J12.1, RV1.2
unnamed: J1.A5 (CC1), R6.1
unnamed: J1.B5 (CC2), R7.1
unnamed: J1.A6 (D+), J1.B6 (D+), R35.2, U6.3 (I/O2)
unnamed: J1.A7 (D-), J1.B7 (D-), U6.1 (I/O1)
unnamed: Q3.1 (G), R50.1, R51.1
unnamed: Q4.1 (G), R52.1, R53.1
unnamed: R26.2, R27.1
unnamed: R27.2, Vsns1.1
unnamed: R28.2, R29.2, Vsns1.4
unnamed: R36.2, Vsns2.1
unnamed: R38.1, R39.1, Vsns2.4
unnamed: F4.2, U4.1 (AC/L)
unnamed: FB1.1, J1.A4 (VBUS), J1.A9 (VBUS), J1.B4 (VBUS), J1.B9 (VBUS), U6.5 (VBUS)
PE: J6.2, J14.2
RLY_CH1: R50.2, U2.24 (IO47)
RLY_CH2: R52.2, U2.25 (IO48)
SCLK: J17.10, J18.10, U2.20 (IO12)
VN1: C42.1, J17.5, R34.1
VN2: C43.1, J18.5, R37.1
VP1: C39.1, J17.6, R29.1
VP2: C44.1, J18.6, R39.2
ZX1: J17.12, U2.9 (IO16)
ZX2: J18.12, U2.23 (IO21)
